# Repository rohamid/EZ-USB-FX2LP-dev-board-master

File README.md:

# EZ USB FX2LP Development board
EZ USB FX2LP CY7C68013A Development board

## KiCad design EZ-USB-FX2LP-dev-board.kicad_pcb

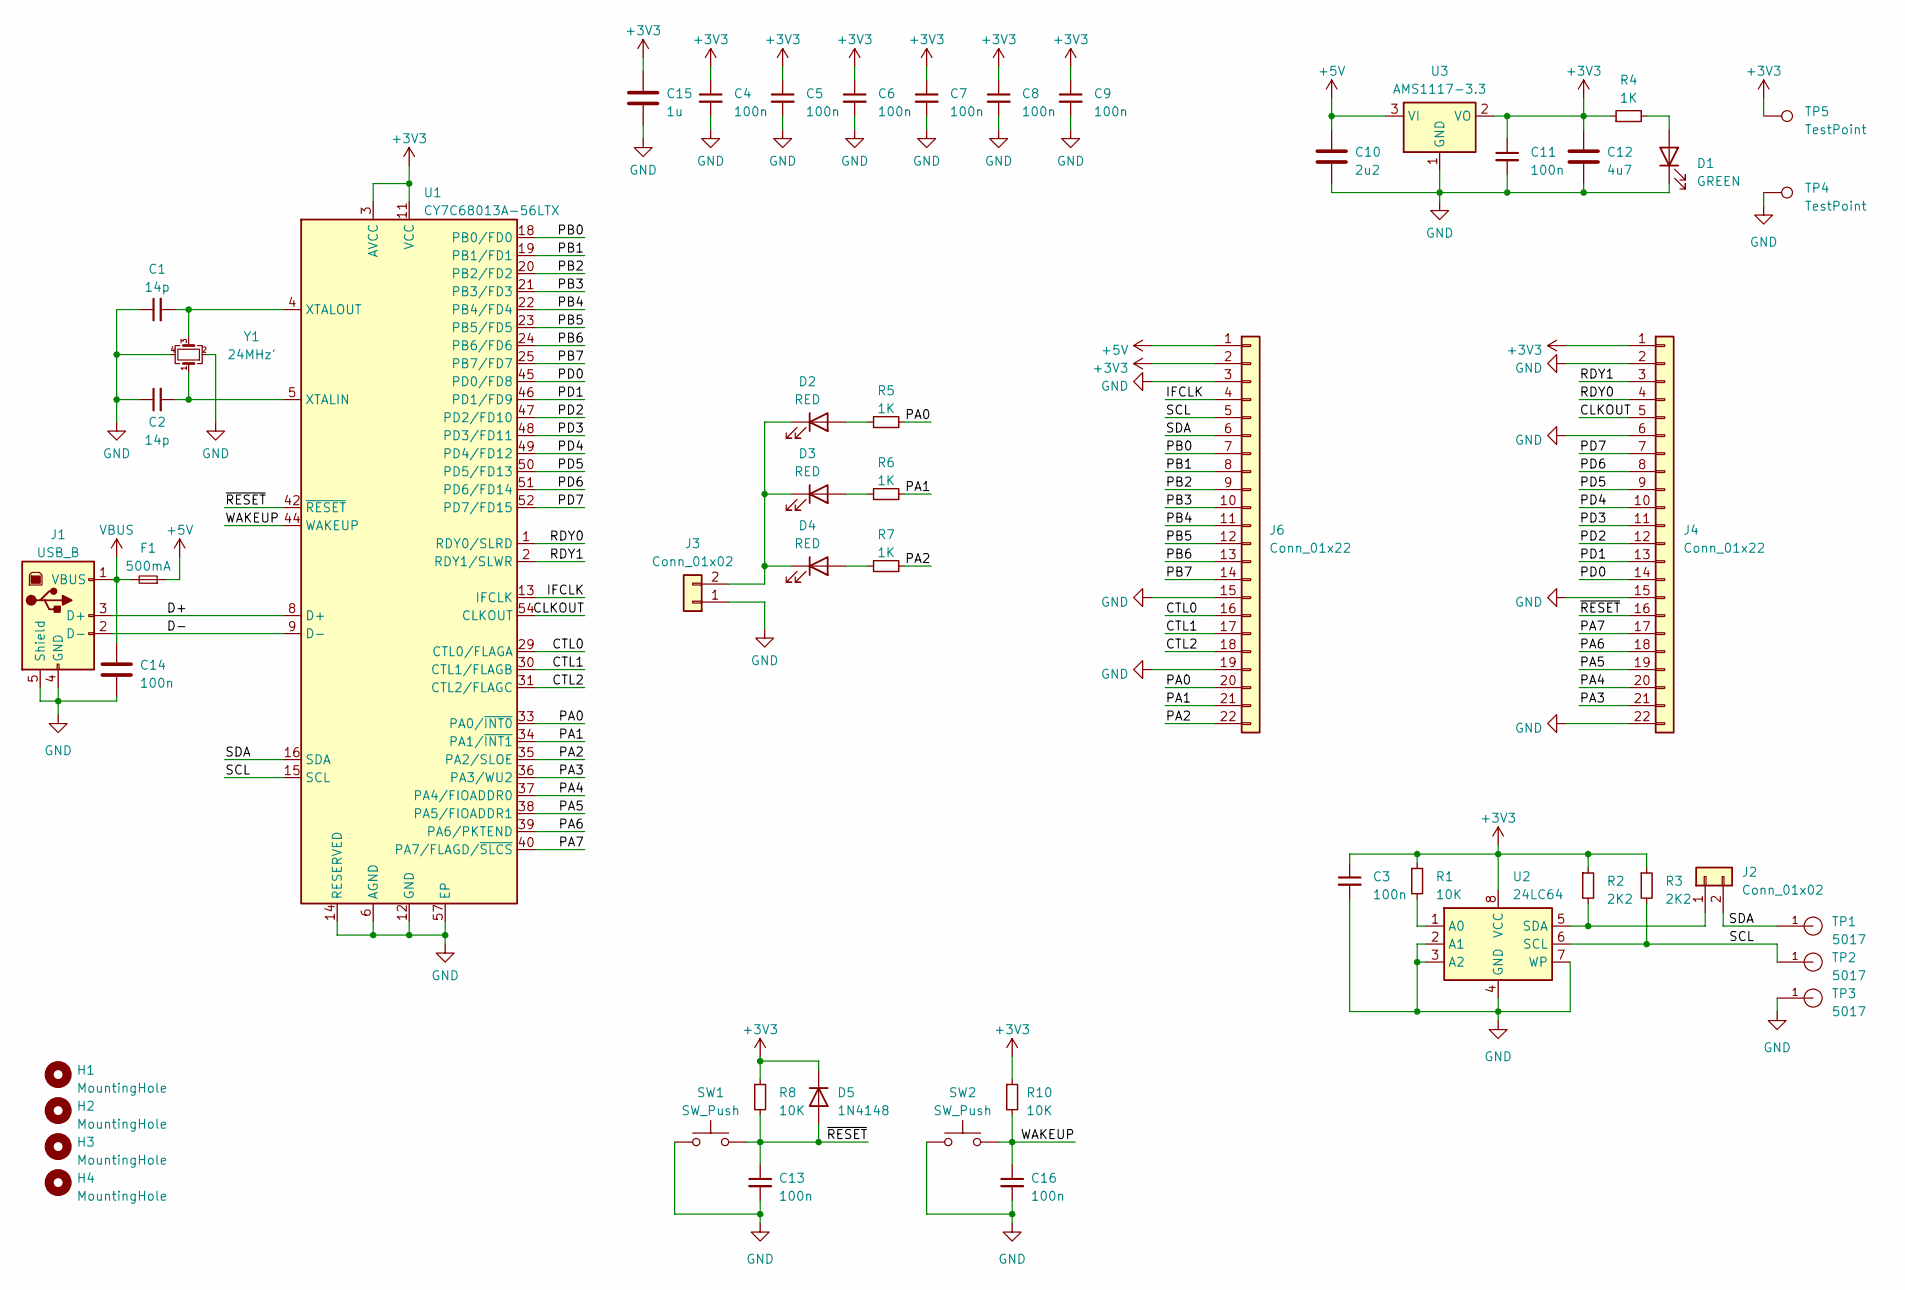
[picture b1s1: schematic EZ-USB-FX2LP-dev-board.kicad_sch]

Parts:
C1, C2: 14p; C_0402_1005Metric; LCSC Part Number C1547
C3, C4, C5, C6, C7, C8, C9, C11, C13, C16: 100n; C_0402_1005Metric; LCSC Part Number C1525
C10: 2u2; C_0805_2012Metric; LCSC Part Number C49217
C12: 4u7; C_0805_2012Metric; LCSC Part Number C1779
C14: 100n; C_0805_2012Metric; LCSC Part Number C28233
C15: 1u; C_0603_1608Metric; LCSC Part Number C15849
D1: GREEN; LED_0805_2012Metric; LCSC Part Number C2297
D2, D3, D4: RED; LED_0805_2012Metric; LCSC Part Number C84256
D5: 1N4148; D_SOD-123; LCSC Part Number C81598
F1: 500mA; Fuse_0805_2012Metric; LCSC Part Number C66452
H1, H2, H3, H4: MountingHole; MountingHole_3.2mm_M3
J1: USB_B; USB_B_OST_USB-B1HSxx_Horizontal
J2, J3: Conn_01x02; PinHeader_1x02_P2.54mm_Vertical
J4, J6: Conn_01x22; PinHeader_1x22_P2.54mm_Vertical
R1, R8, R10: 10K; R_0402_1005Metric; LCSC Part Number C25744
R2, R3: 2K2; R_0402_1005Metric; LCSC Part Number C25879
R4, R5, R6, R7: 1K; R_0402_1005Metric; LCSC Part Number C11702
SW1, SW2: SW_Push; SW_Push_1P1T_NO_Vertical_Wuerth_434133025816; LCSC Part Number C127488
TP1, TP2, TP3: 5017; Keystone_5017_testring; PARTREV E; LCSC Part Number C238130
TP4, TP5: TestPoint; TestPoint_Pad_D1.0mm
U1: CY7C68013A-56LTX; QFN-56-1EP_8x8mm_P0.5mm_EP4.5x5.2mm_ThermalVias_TopTented; LCSC Part Number C14912
U2: 24LC64; SOIC-8_3.9x4.9mm_P1.27mm; LCSC Part Number C92359
U3: AMS1117-3.3; SOT-223-3_TabPin2; LCSC Part Number C6186
Y1: 24MHz'; Crystal_SMD_3225-4Pin_3.2x2.5mm; LCSC Part Number C2650460

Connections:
+3V3: C3.1, C4.1, C5.1, C6.1, C7.1, C8.1, C9.1, C11.1, C12.1, C15.1, D5.1 (K), J4.1, J6.2, R1.1, R2.1, R3.1, R4.1, R8.1, R10.1, TP5.1, U1.3 (AVCC), U1.7 (AVCC), U1.11 (VCC), U1.17 (VCC), U1.27 (VCC), U1.32 (VCC), U1.43 (VCC), U1.55 (VCC), U2.8 (VCC), U3.2 (VO)
+5V: C10.1, F1.1, J6.1, U3.3 (VI)
/CLKOUT: J4.5, U1.54 (CLKOUT)
/CTL0: J6.16, U1.29 (CTL0/FLAGA)
/CTL1: J6.17, U1.30 (CTL1/FLAGB)
/CTL2: J6.18, U1.31 (CTL2/FLAGC)
/D+: J1.3 (D+), U1.8 (D+)
/D-: J1.2 (D-), U1.9 (D-)
/IFCLK: J6.4, U1.13 (IFCLK)
/PA0: J6.20, R5.2, U1.33 (PA0/~INT0)
/PA1: J6.21, R6.2, U1.34 (PA1/~INT1)
/PA2: J6.22, R7.2, U1.35 (PA2/SLOE)
/PA3: J4.21, U1.36 (PA3/WU2)
/PA4: J4.20, U1.37 (PA4/FIOADDR0)
/PA5: J4.19, U1.38 (PA5/FIOADDR1)
/PA6: J4.18, U1.39 (PA6/PKTEND)
/PA7: J4.17, U1.40 (PA7/FLAGD/~SLCS)
/PB0: J6.7, U1.18 (PB0/FD0)
/PB1: J6.8, U1.19 (PB1/FD1)
/PB2: J6.9, U1.20 (PB2/FD2)
/PB3: J6.10, U1.21 (PB3/FD3)
/PB4: J6.11, U1.22 (PB4/FD4)
/PB5: J6.12, U1.23 (PB5/FD5)
/PB6: J6.13, U1.24 (PB6/FD6)
/PB7: J6.14, U1.25 (PB7/FD7)
/PD0: J4.14, U1.45 (PD0/FD8)
/PD1: J4.13, U1.46 (PD1/FD9)
/PD2: J4.12, U1.47 (PD2/FD10)
/PD3: J4.11, U1.48 (PD3/FD11)
/PD4: J4.10, U1.49 (PD4/FD12)
/PD5: J4.9, U1.50 (PD5/FD13)
/PD6: J4.8, U1.51 (PD6/FD14)
/PD7: J4.7, U1.52 (PD7/FD15)
/RDY0: J4.4, U1.1 (RDY0/SLRD)
/RDY1: J4.3, U1.2 (RDY1/SLWR)
/SCL: J6.5, R3.2, TP2.1, U1.15 (SCL), U2.6 (SCL)
/SDA: J2.2, J6.6, TP1.1, U1.16 (SDA)
/WAKEUP: C16.1, R10.2, SW2.2, U1.44 (WAKEUP)
/~RESET: C13.1, D5.2 (A), J4.16, R8.2, SW1.2, U1.42 (~RESET)
GND: C1.1, C2.1, C3.2, C4.2, C5.2, C6.2, C7.2, C8.2, C9.2, C10.2, C11.2, C12.2, C13.2, C14.2, C15.2, C16.2, D1.1 (K), J1.4 (GND), J1.5 (Shield), J3.1, J4.2, J4.6, J4.15, J4.22, J6.3, J6.15, J6.19, SW1.1, SW2.1, TP3.1, TP4.1, U1.6 (AGND), U1.10 (AGND), U1.12 (GND), U1.14 (RESERVED), U1.26 (GND), U1.28 (GND), U1.41 (GND), U1.53 (GND), U1.56 (GND), U1.57 (EP), U2.2 (A1), U2.3 (A2), U2.4 (GND), U2.7 (WP), U3.1 (GND), Y1.2, Y1.4
unnamed: D1.2 (A), R4.2
unnamed: D2.2 (A), R5.1
unnamed: D2.1 (K), D3.1 (K), D4.1 (K), J3.2
unnamed: D3.2 (A), R6.1
unnamed: D4.2 (A), R7.1
unnamed: J2.1, R2.2, U2.5 (SDA)
unnamed: C2.2, U1.5 (XTALIN), Y1.1
unnamed: C1.2, U1.4 (XTALOUT), Y1.3
unnamed: R1.2, U2.1 (A0)
VBUS: C14.1, F1.2, J1.1 (VBUS)

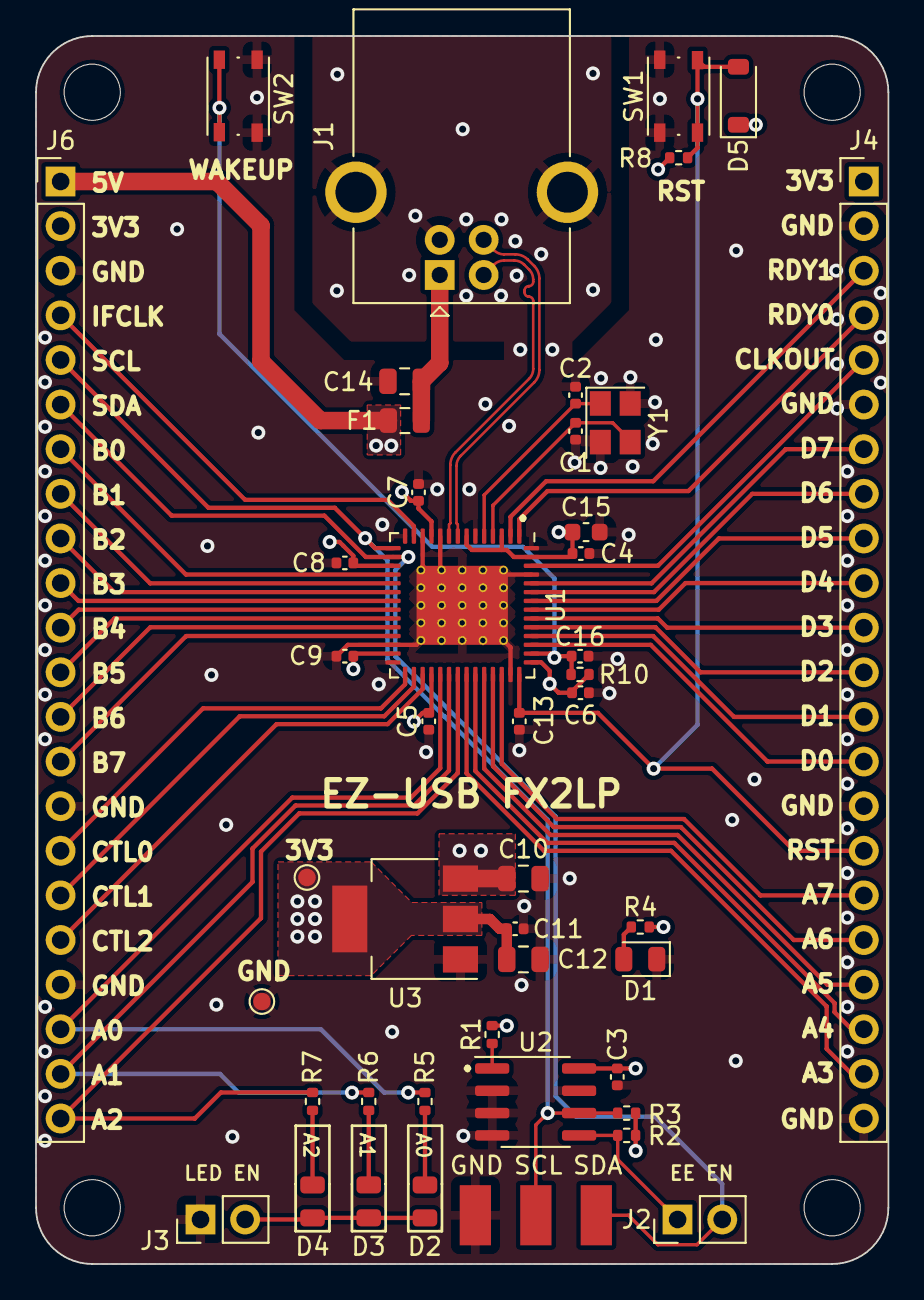
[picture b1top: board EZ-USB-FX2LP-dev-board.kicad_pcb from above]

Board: 4 copper layers, 48.5 x 69.9 mm, 51 parts (0 on the bottom side), 50 nets.

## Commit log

2024-02-18 Initial Status
